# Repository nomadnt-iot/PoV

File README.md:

- [What is a PoV display](#what-is-a-pov-display)
- [Introduction](#introduction)
- [How it's work](#how-its-work)
  - [Output pins](#output-pins)
  - [Display text](#display-text)
- [Hardware](#hardware)
  - [Components used](#components-used)
- [Useful links](#useful-links)
- [TODO](#todo)

# What is a PoV display

[Here](https://en.wikipedia.org/wiki/Persistence_of_vision) the definition of Persistence of Vision Display from wikipedia.

*The term "persistence of vision display" or "POV display" has been used for LED display devices that compose images by displaying one spatial portion at a time in rapid succession, (for example, one column of pixels every few milliseconds). A two-dimensional POV display is often accomplished by means of rapidly moving a single row of LEDs along a linear or circular path. The effect is that the image is perceived as a whole by the viewer as long as the entire path is completed during the visual persistence time of the human eye. A further effect is often to give the illusion of the image floating in mid-air.*

A common example of this can be seen in the use of bicycle wheel lights that produce patterns.

# Introduction

**PoV** is a very simple **P**ersistent **o**f **V**ision display based on Atmel ATTinyX5 chips family.
It is making use of all 5 pins available on ATTinyX5 chips family and it is written in pure AVR-C.

# How it's work

The ATTinyX5 has only 5 GPIO pins suitable to drive our display. The [Schematic](hardware/schematic.pdf) will help you to better understand how leds are connected to each pin.

It is using only 16 bytes of RAM and 634 bytes of Flash memory

```sh
RAM:   [          ]   3.1% (used 16 bytes from 512 bytes)
Flash: [=         ]   7.7% (used 634 bytes from 8192 bytes)
```

## Output pins

First we have to set all the 5 pins on the ATTinyX5 as output.

```c
#include <pov.h>

int main(void)
{
    DDRB = 0x1F; // 0x1F is equals to 31 that is equals to 1 << 5
    ...
}
```

## Display text

In order to display text we need to call the `display` method in a loop like the following

```c
#include <pov.h>

int main(void)
{
    DDRB = 0x1F; // 0x1F is equals to 31 that is equals to 1 << 5

    while (1)
    {
        display("jacopo sallemi", 2, 5);
    }
}
```

Than the `display` function is looping through all the chars in the string and call the `display_char` method that is just getting the encoded corrisponding `value` related to the processed char and than configure the `PORTB` in accoding to the value.

```c
void display_char(const char c, unsigned char delayTime, unsigned char charBreak)
{
    for (unsigned char i = 0; i < (sizeof(symbols) / sizeof(struct symbol_t)); i++)
    {
        if (c == pgm_read_byte(&symbols[i].code))
        {
            for (unsigned char j = 0; j < COLS_COUNT; j++)
            {
                // Configure PORTB with the current encoded value
                PORTB = pgm_read_byte(&symbols[i].value[j]);
                _delay_ms(delayTime);
            }

            // Turn off all the output
            PORTB = 0;
        }
    }

    _delay_ms(charBreak);
}
```

# Hardware 

The [Hardware](hardware) folder contains my first eagle implementation and a new version based on KiKad.
Anyways you can use both of them as starting point to your PoV project. 

- [Schematic](hardware/schematic.pdf)
- [3D model](hardware/PoV.png)

## Components used

- 1x ATTinyX5
- 5x leds green
- 1x 100 nF decoupling capacitor
- 1x switch
- 1x R2032
- 1x battery holder for CR2032
- Stripboard
- Some soldering cable

The circuit is power by a CR2032 so this is the reason for the switch... to turn on and off the PoV as required.  
The decoupling capacitor is always a good idea to have expecially when we are powering devices through battery and is connected as closet as possible the ATTinyX5.  
And finally The leds are all connected from the bottom to the top to the ATTinyX5's pins PB0, PB1, PB2, PB3, PB4.

```
LEDS CONNECTION

            PB4 [] LED5

            PB3 [] LED4

            PB2 [] LED3

            PB1 [] LED2

            PB0 [] LED1

              +-\/-+
        PB5  1|    |8   VCC
(LED4)  PB3  2|    |7   PB2  (LED3)
(LED5)  PB4  3|    |6   PB1  (LED2)
        GND  4|    |5   PB0  (LED1)
              +----+

```

The ATTinyX5 has only `PORTB` and can handle only 5 GPIO so [symbols.h](include/symbols.h) is provided to handle only char 5x5 pixels.  
Feel free to change it in according to your requirements.

# Useful links

- [Programming AVR Microcontrollers in C - O'Reilly Webcast](https://youtu.be/ERY7d7W-6nA)
- [Font 5x5 pixel resource 1](https://www.dafont.com/5x5.font)
- [Font 5x5 pixel resource 2](https://www.1001fonts.com/5x5-font.html)
- [ATTinyX5 Datasheet](https://ww1.microchip.com/downloads/en/DeviceDoc/Atmel-2586-AVR-8-bit-Microcontroller-ATtiny25-ATtiny45-ATtiny85_Datasheet.pdf)

# TODO

- make code non blocking
- add V-USB support for micronucleous firmare.
- reorganize fonts

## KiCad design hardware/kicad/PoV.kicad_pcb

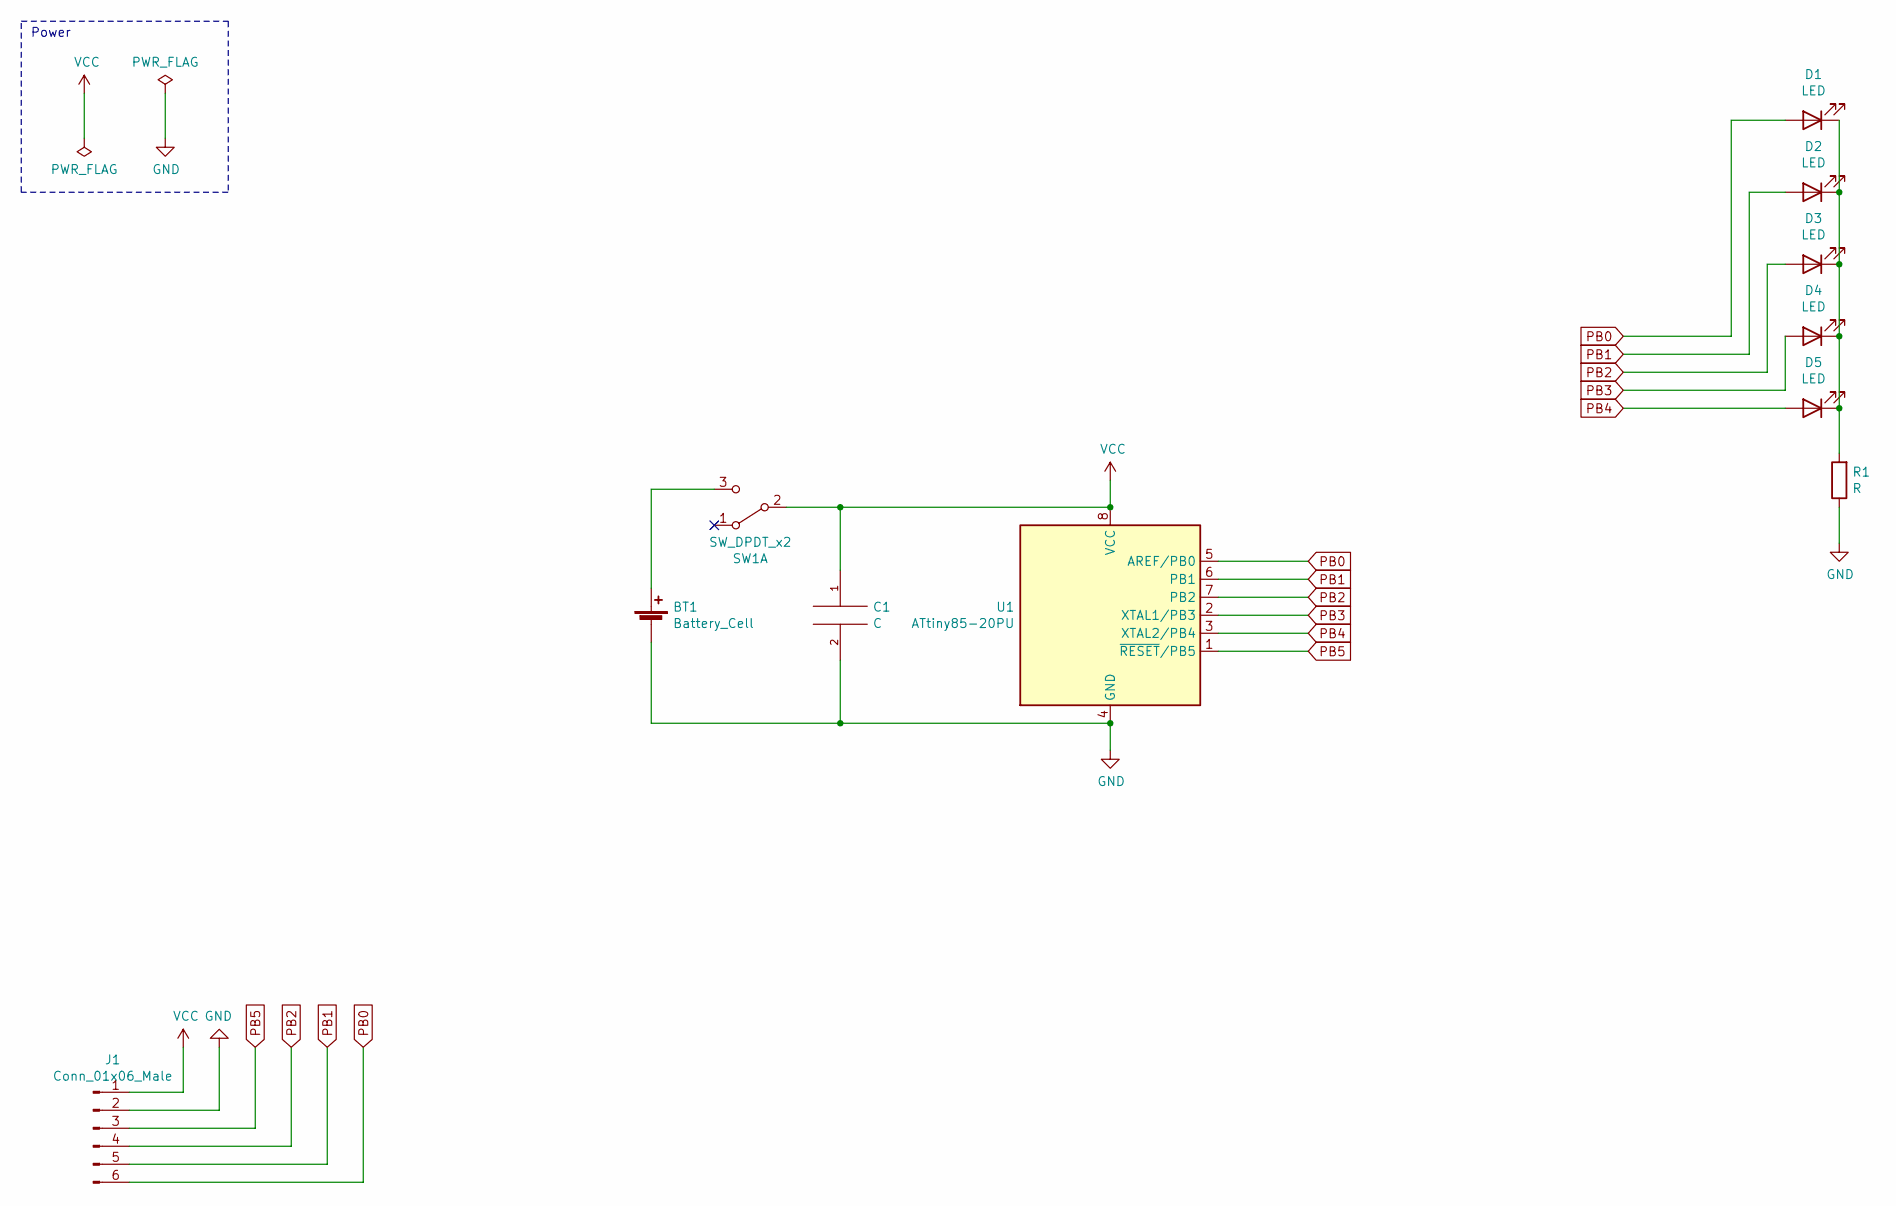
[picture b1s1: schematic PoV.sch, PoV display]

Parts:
BT1: Battery_Cell; BatteryHolder_Keystone_103_1x20mm
C1: C; C_Disc_D3.0mm_W1.6mm_P2.50mm
D1, D2, D3, D4, D5: LED; LED_D5.0mm
J1: Conn_01x06_Male; PinHeader_1x06_P2.54mm_Vertical
R1: R; R_Axial_DIN0207_L6.3mm_D2.5mm_P7.62mm_Horizontal
SW1: SW_DPDT_x2; SW_CuK_JS202011AQN_DPDT_Angled
U1: ATtiny85-20PU; DIP-8_W7.62mm

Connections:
GND: BT1.2 (-), C1.2, J1.2, R1.1, U1.4 (GND)
unnamed: BT1.1 (+), SW1.3 (C)
unnamed: D1.1 (K), D2.1 (K), D3.1 (K), D4.1 (K), D5.1 (K), R1.2
PB0: D1.2 (A), J1.6, U1.5 (AREF/PB0)
PB1: D2.2 (A), J1.5, U1.6 (PB1)
PB2: D3.2 (A), J1.4, U1.7 (PB2)
PB3: D4.2 (A), U1.2 (XTAL1/PB3)
PB4: D5.2 (A), U1.3 (XTAL2/PB4)
PB5: J1.3, U1.1 (~RESET~/PB5)
VCC: C1.1, J1.1, SW1.2 (B), U1.8 (VCC)

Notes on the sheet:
Power

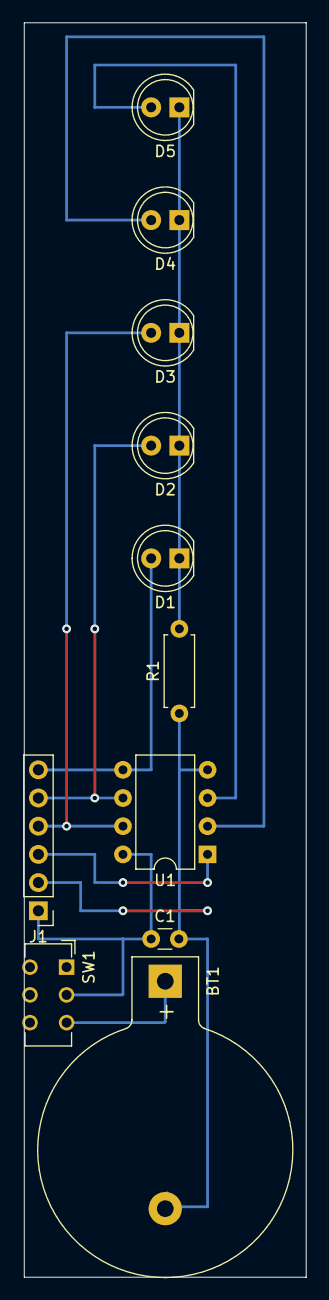
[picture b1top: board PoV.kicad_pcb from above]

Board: 2 copper layers, 25.4 x 113.0 mm, 11 parts (0 on the bottom side), 10 nets.

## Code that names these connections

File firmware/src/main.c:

/**
 *  PoV is a very simple persistent of vision display that use ATTiny85 and 5 leds
 */
#include <util/delay.h>
#include <hardware.h>
#include <uPoV.h>

// defining led array
unsigned char LED[LEDS_COUNT] = {PB4, PB3, PB2, PB1, PB0};

int main(void)
{
    // Heremany ways how to assign pin a outout 
    // LEDS_DDR |= (_BV(PB0) | _BV(PB1) | _BV(PB2) | _BV(PB3) | _BV(PB4));
    // LEDS_DDR = 0x1F;
    // LEDS_DDR = 32;
    // LEDS_DDR = (1 << LEDS_COUNT) - 1;

    for (unsigned char i = 0; i < LEDS_COUNT; i++)
    {
        _sbi(LEDS_PORT, LED[i]);
        _delay_ms(250);
    }

    for (unsigned char i = LEDS_COUNT; i > 0; i--)
    {
        _cbi(LEDS_PORT, LED[i - 1]);
        _delay_ms(250);
    }

    while (1)
    {
        display(LED, "jacopo sallemi", 2, 5);
    }
}

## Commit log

2017-10-22 initial import
2017-10-22 removed digispark from patrformio and optimize memory usage using uint8_t instead of int
2017-10-22 added alphabet header file for code organizing
2017-10-22 moved everithing to library uPoV
2017-10-22 massive use of progmem for alphabet and gain more more space
2017-11-01 added digispark-tiny support
2018-02-25 remove unused code and init support for trinket
2018-09-23 reorganizing project directory
2018-10-21 improving code organization and documentation
2018-10-22 added bitwise operation to turn on and off the leds line
2018-10-24 init to work on new symbols
2019-05-25 updating eagle files
2019-05-26 updating symbols table
2019-05-26 fixed fonts
2021-09-25 move uPoV as a library
2021-09-25 improved readme
2021-09-26 working on initial version avr-c
2021-09-26 make pov working with avr-c
2021-09-26 removed wrong led array
2021-09-26 sync
2021-09-26 last stable
2021-09-26 shrink the code as much as possible
2021-09-26 reorganizing layout
2021-09-26 improve readme
2021-09-27 improving doc
2021-09-27 move eagle files inside eagle folder
2021-09-27 added kicad schematic
2021-09-27 updated kicad schematic
2021-09-27 woking on kicad
2021-09-27 improved kicad project
2021-09-27 added first schematic draw
2021-09-27 removed todo section
2021-09-27 imrpving readme
2021-09-27 added table of contents
2021-10-01 added missed route on pcb
2021-10-01 improved design
2021-10-04 improve readme and optimize code
2021-10-10 now pov is programmable from board
